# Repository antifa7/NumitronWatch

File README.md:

# NumitronWatch
A work in progress. ATMega328P controlled IV-16 tube two digit watch

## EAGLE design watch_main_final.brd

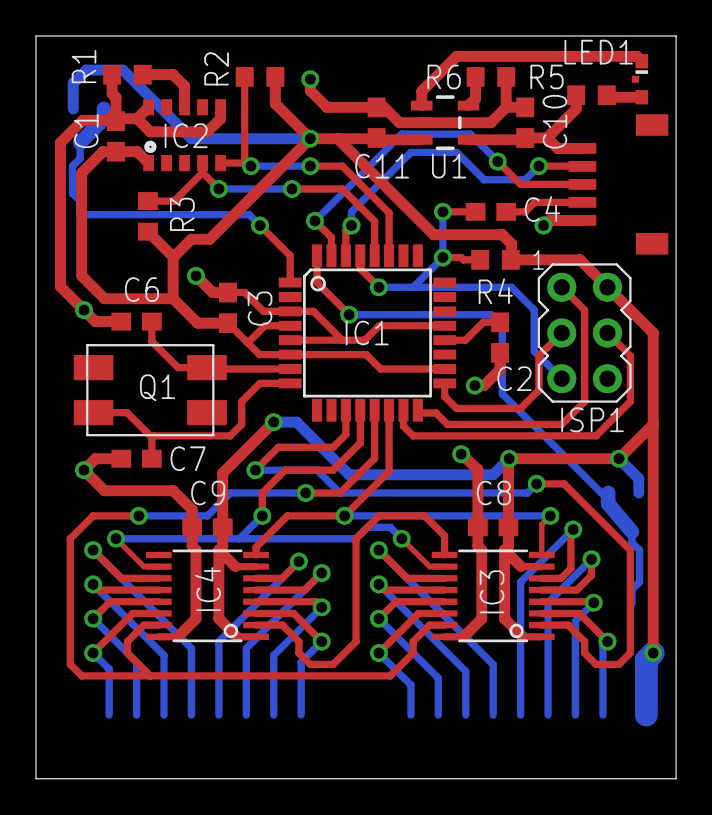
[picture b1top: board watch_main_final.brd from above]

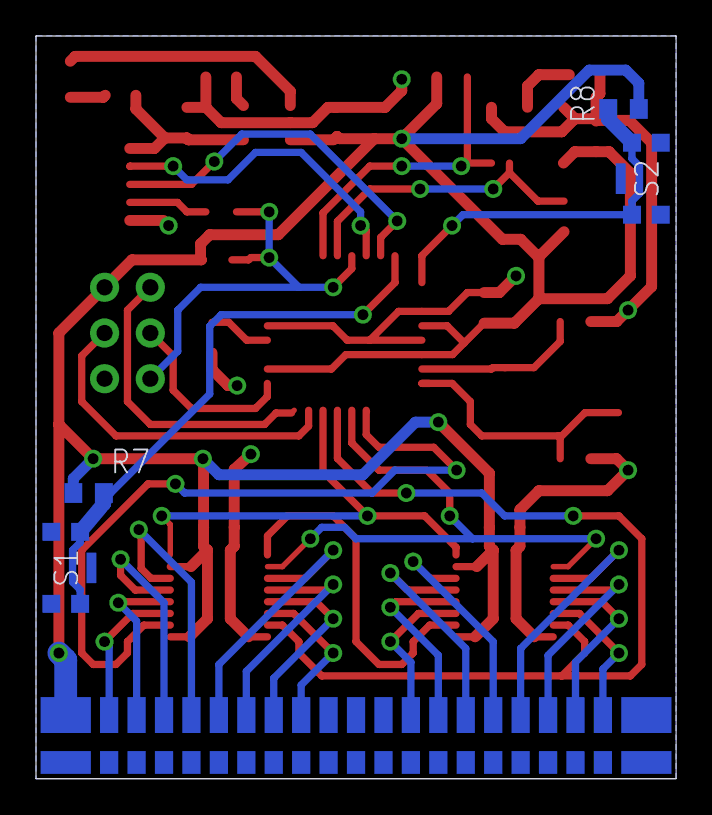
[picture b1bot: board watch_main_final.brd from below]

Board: 2 copper layers, 35.6 x 41.3 mm, 30 parts (5 on the bottom side), 42 nets.

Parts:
C1: 10n; C0603
C2, C3, C4, C8, C9: 100n; C0603
C6, C7: 22pF; C0603
C10, C11: 4.7uF; C0603
CONN1: SM05B-SRSS-TB; JST-SR-SIDE-5
CONN2: PCBMOUNT-20; PCBMOUNT-VERTICAL-20
IC1: MEGA8-AI; TQFP32-08
IC2: RV-3029; RV-3029-C2
IC3, IC4: TLC6C598-Q1; TSSOP-16
ISP1: AVRISP-6; AVRISP
LED1: LED-0603-SIDE-FLIPPED
Q1: 8MHz; MQ
R1, R4, R7, R8: 10K; R0603
R2, R3: 4,7K; R0603
R5: 155; R0603
R6: 5K; R0603
S1, S2: KMSXXXG; C&K-KMS-SWITCH
U1: MCP73831; SOT23-5

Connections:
AREF: C2.1, IC1.20
CLOCK: IC1.13, IC3.15, IC4.15
DATA: IC1.11, IC3.2
ENABLE: IC1.14, IC3.8, IC4.8
GND: C1.2, C2.2, C3.2, C6.1, C7.1, C8.2, C9.2, C10.1, C11.1, CONN1.5, CONN2.P2, IC1.3, IC1.5, IC1.21, IC2.6, IC2.10, IC3.16, IC4.16, ISP1.6, R1.1, R6.2, S1.1, S1.5, S2.1, S2.5, U1.2
LATCH: IC1.12, IC3.10, IC4.10
MISO: IC1.16, ISP1.1
MOSI: IC1.15, ISP1.4
unnamed: IC2.8, R1.2
unnamed: IC3.9, IC4.2
unnamed: C6.2, IC1.7, Q1.P3
unnamed: C7.2, IC1.8, Q1.P1
unnamed: LED1.C, U1.1
unnamed: LED1.A, R5.1
unnamed: R6.1, U1.5
unnamed: C4.2, CONN1.4
RST: C4.1, IC1.29, ISP1.5, R4.2
RX: CONN1.2, IC1.30
SCK: IC1.17, ISP1.3
SCL: IC1.28, IC2.4, R3.1
SDA: IC1.27, IC2.5, R2.1
SW1: IC1.32, R7.1, S1.2, S1.4
SW2: IC1.1, R8.1, S2.2, S2.4
TUBE1_1: CONN2.1, IC3.3
TUBE1_2: CONN2.2, IC3.4
TUBE1_3: CONN2.3, IC3.5
TUBE1_4: CONN2.4, IC3.6
TUBE1_5: CONN2.5, IC3.11
TUBE1_6: CONN2.6, IC3.12
TUBE1_7: CONN2.7, IC3.13
TUBE1_8: CONN2.8, IC3.14
TUBE2_1: CONN2.12, IC4.3
TUBE2_2: CONN2.13, IC4.4
TUBE2_3: CONN2.14, IC4.5
TUBE2_4: CONN2.15, IC4.6
TUBE2_5: CONN2.16, IC4.11
TUBE2_6: CONN2.17, IC4.12
TUBE2_7: CONN2.18, IC4.13
TUBE2_8: CONN2.19, IC4.14
TX: CONN1.3, IC1.31
VCC: C1.1, C3.1, C8.1, C9.1, C11.2, CONN2.P1, IC1.4, IC1.6, IC1.18, IC2.1, IC3.1, IC3.7, IC4.1, IC4.7, ISP1.2, R2.2, R3.2, R4.1, R7.2, R8.2, U1.3
VCC/2: C10.2, CONN1.1, R5.2, U1.4

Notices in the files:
parts and their libraries:
SparkFun-PowerIC: Licensing: CC v3.0 Share-Alike You are welcome to use this library for commercial purposes.
